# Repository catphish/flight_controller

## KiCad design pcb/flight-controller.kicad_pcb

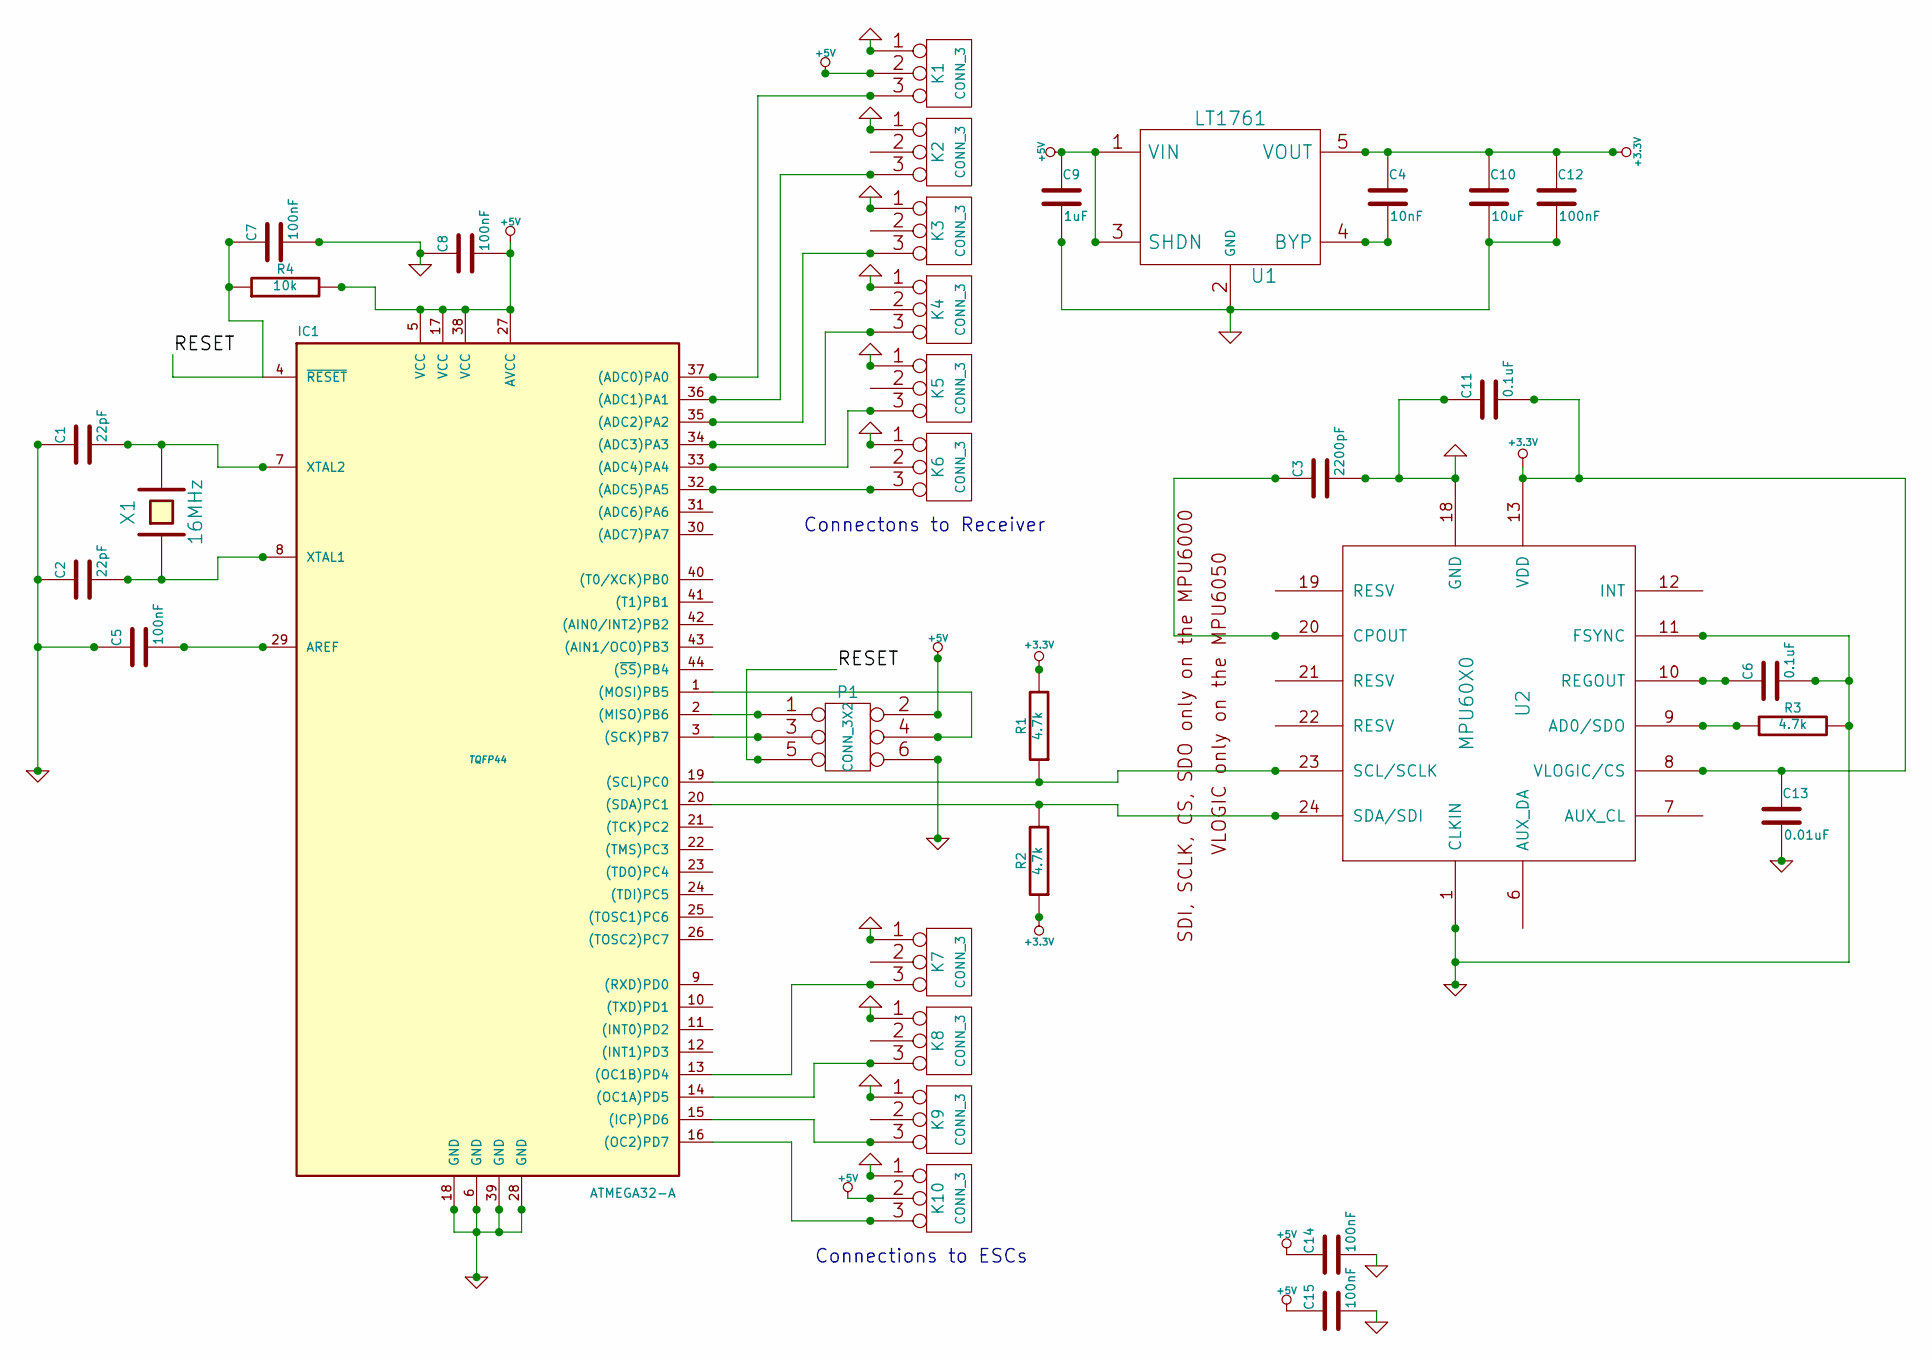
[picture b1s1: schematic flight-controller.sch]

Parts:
C1, C2: 22pF
C3: 2200pF
C4: 10nF
C5, C7, C8, C12, C14, C15: 100nF
C6, C11: 0.1uF
C9: 1uF
C10: 10uF
C13: 0.01uF
IC1: ATMEGA32-A; TQFP44
K1, K2, K3, K4, K5, K6, K7, K8, K9, K10: CONN_3
P1: CONN_3X2
R1, R2, R3: 4.7k
R4: 10k
U1: LT1761
U2: MPU60X0
X1: 16MHz

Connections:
+3.3V: C4.1, C10.1, C11.2, C12.1, C13.1, R1.2, R2.1, U1.5 (VOUT), U2.8 (VLOGIC/CS), U2.13 (VDD)
+5V: C8.2, C9.1, C14.1, C15.1, IC1.5 (VCC), IC1.17 (VCC), IC1.27 (AVCC), IC1.38 (VCC), K1.2 (PM), K10.2 (PM), P1.2, R4.2, U1.1 (VIN), U1.3 (SHDN)
/RESET: C7.1, IC1.4 (~RESET), P1.5, R4.1
GND: C1.1, C2.1, C3.2, C5.1, C6.2, C7.2, C8.1, C9.2, C10.2, C11.1, C12.2, C13.2, C14.2, C15.2, IC1.6 (GND), IC1.18 (GND), IC1.28 (GND), IC1.39 (GND), K1.1, K2.1, K3.1, K4.1, K5.1, K6.1, K7.1, K8.1, K9.1, K10.1, P1.6, R3.2, U1.2 (GND), U2.1 (CLKIN), U2.11 (FSYNC), U2.18 (GND)
unnamed: IC1.13 ((OC1B)PD4), K7.3
unnamed: IC1.14 ((OC1A)PD5), K8.3
unnamed: C5.2, IC1.29 (AREF)
unnamed: IC1.20 ((SDA)PC1), R2.2, U2.24 (SDA/SDI)
unnamed: IC1.19 ((SCL)PC0), R1.1, U2.23 (SCL/SCLK)
unnamed: IC1.37 ((ADC0)PA0), K1.3
unnamed: IC1.36 ((ADC1)PA1), K2.3
unnamed: IC1.35 ((ADC2)PA2), K3.3
unnamed: IC1.34 ((ADC3)PA3), K4.3
unnamed: IC1.33 ((ADC4)PA4), K5.3
unnamed: IC1.32 ((ADC5)PA5), K6.3
unnamed: IC1.16 ((OC2)PD7), K10.3
unnamed: C3.1, U2.20 (CPOUT)
unnamed: IC1.1 ((MOSI)PB5), P1.4
unnamed: C6.1, U2.10 (REGOUT)
unnamed: R3.1, U2.9 (AD0/SDO)
unnamed: C4.2, U1.4 (BYP)
unnamed: IC1.2 ((MISO)PB6), P1.1
unnamed: IC1.3 ((SCK)PB7), P1.3
unnamed: C1.2, IC1.7 (XTAL2), X1.2
unnamed: IC1.15 ((ICP)PD6), K9.3
unnamed: C2.2, IC1.8 (XTAL1), X1.1

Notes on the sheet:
Connections to ESCs
Connectons to Receiver

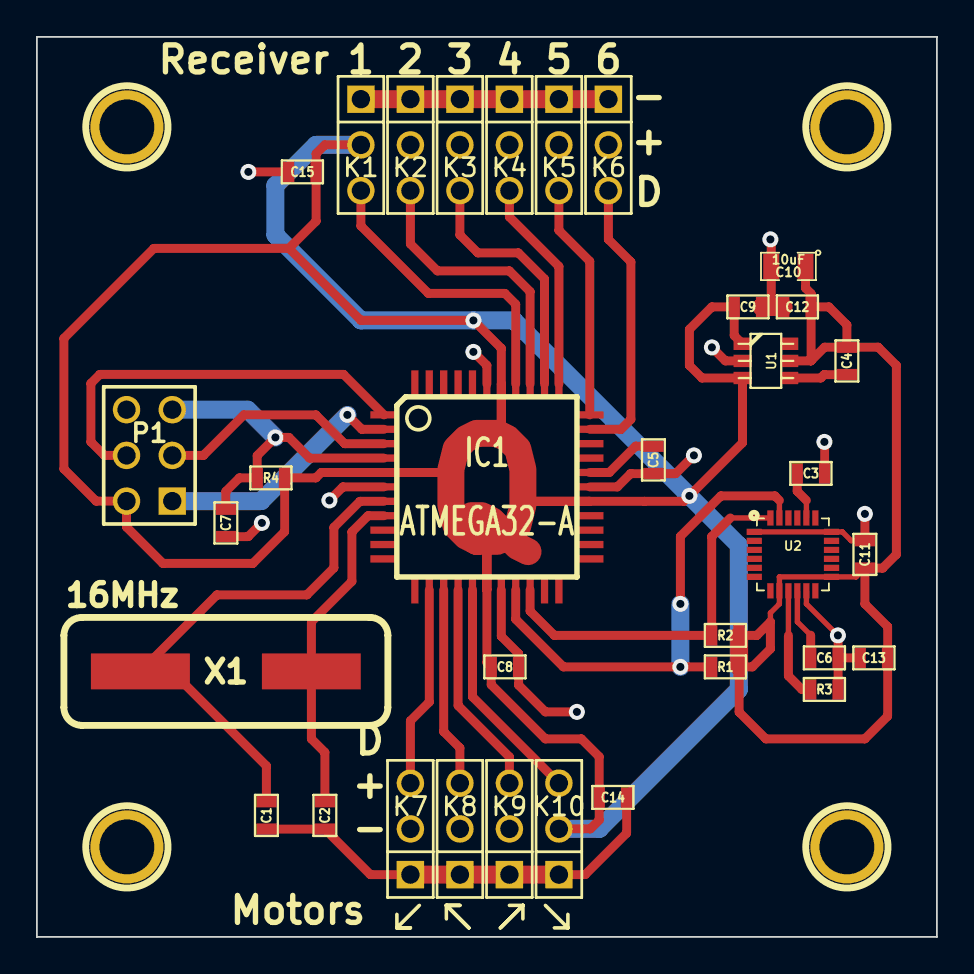
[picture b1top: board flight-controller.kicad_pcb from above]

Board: 2 copper layers, 50.0 x 50.0 mm, 34 parts (0 on the bottom side), 26 nets.

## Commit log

2013-11-17 Initial attempt with R/C and basic stabilization
2013-11-17 lots of work, partially functional / tested stabilization, currently FWD
2013-11-18 add a proper PID algorithm because my stabilization sucked, untested
2013-11-18 tune the thingy
2013-11-18 today i learned motor speeds reduce with battery voltage, we need to scale everything together
2013-11-23 rewrite motor and radio code for speed / accuracy
2013-11-23 fuck me, it's stable like this
2013-11-23 tidying, adjustments proportional to throttle
2013-11-23 minor tweaks
2013-11-24 live pid graphs, don't adjust pid when idling
2013-11-26 disable slow barometer, insert some simple PID values, add z stabilization
2013-11-26 battery voltage read
2013-11-26 high speed barometer code, remove ineffective z-compensation
2013-11-28 small tidy
2013-11-28 major refactor, remove 3rd party PID, extract libraries
2013-11-28 remove hardcoded test value
2013-11-28 i'm committing because i just had an actual successful flight!
2013-11-28 add z stabilization and control
2013-11-28 don't invert Y axis, that causes pain when you try to fly it away from your face
2013-11-28 these were way too sensitive
2013-11-29 correct fatal error with reversed gyro, increase control sensitivity
2013-12-01 tidy up, add scope for I term on z drift
2013-12-03 tidy things up, remove unused code, add 6-channel receiver, add kill switch to allow further reductions in throttle sensitivity
2013-12-03 further tidying
2013-12-03 remove failed altitude experimental code
2013-12-06 adjust controller responses
2013-12-07 altitude hold
2013-12-07 remove altitude hold, this isn't working well
2013-12-07 increase control sensitivity
2013-12-07 large increases to control and feedback responsiveness
2013-12-07 further pid tuning
2013-12-07 more pid tuning, we can now achieve stable flight, with all controls being very rsonsive and the throttle still a little oversensitive
2013-12-08 add compass, not currently accurate
2013-12-08 re-add altitude hold, this isn't tested, but will only be active if enabled from the RC
2013-12-10 lots of work on altitude control, UNTESTED
2013-12-12 Revert "lots of work on altitude control, UNTESTED"
    This reverts commit 00f80fb907816c0848a73623b2992b4bc48d4b41.
2013-12-12 Revert "re-add altitude hold, this isn't tested, but will only be active if enabled from the RC"
    This reverts commit 7fdb75e066b343deceeb1af1b908b9b1dafb5d2a.
2013-12-13 begin support for echo distance sensor
2013-12-14 more sensitive barometer response
2013-12-14 simultaneous ESC updates for faster and more consistent response, add pitch/roll to throttle to prevent descent when manoeuvring, increse altitude hold sensitivity
2013-12-16 replace BMP085 with MS5611, rework altitude hold
2013-12-22 significant tidying in preparation of basic hardware build
2013-12-22 add schematic / pcb layout
2013-12-22 lots of improvements to flight control and PCB
2013-12-22 add rendered pcb PDFs
2013-12-27 minor improvements, this should improve descent stability
2013-12-29 proper rate based yaw, altitude correction linked to ch6
2013-12-29 documentation and tidying
2013-12-30 finish yaw control, tune altitude correction
2013-12-31 detect upside-down state, reduce yaw correction at extremes of angle
2014-01-06 complete rewrite without arduino
2014-01-09 finish avr version
2014-01-10 adjust gains, use DMP to fetch filtered gyro outputs
2014-03-02 various improvements, currently running on arduino mega
2014-03-02 update copyright notices
2014-03-17 add very simple altitude control using MS5611
2014-03-17 remove pcb for now
2014-03-19 velocity and altitude estimates using apu and baro
2014-03-19 finish baro altitude hold, accurate to approx 1m, may need gain adjustments
2014-03-19 gyro calibration
2014-03-20 final tuning for baro alt. TODO: alt gains (alt vs velocity)
2014-03-22 small tuning adjustments
2014-03-23 increase yaw correction
2014-03-23 tuning
2014-03-26 a slightly different tae on altitude tuning
2014-03-30 new digital rc, small tunings
2014-03-30 small tuning changes, very stable flight, yaw control is a little dangerous
2014-04-01 a totally new take on altitude hold, safer yaw correction, i currently have concerns about pitch/roll integration
2014-04-02 undo some non working things
2014-04-02 Revert "undo some non working things"
    This reverts commit e10c75d29966ebf9c649589e917734910f83a39f.
2014-04-02 Revert "a totally new take on altitude hold, safer yaw correction, i currently have concerns about pitch/roll integration"
    This reverts commit 72d18917e2496c67f50c0db7bd1784adafcd640c.
2014-04-02 sort out some bits
2014-04-05 add compass (probably finished) and gps (not finished)
2014-04-06 pretty sure that was invested!
2014-04-06 calibrate gyro / z-accelerometer
2014-04-06 a little more accelerometer tweaking
2014-04-06 new high resolution compass assisted yaw control, untested, improvements to altitude hold algorithm, untested
2014-04-08 revert previous altitude hold changes, old version was better NOTE: compass way off when pitching forward/back NOTE: GPS seems to work, but inaccurate due to compass pitch issue NOTE: GPS adjustments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
2014-04-10 tidy, this isn't going to work without a 10DOF board
2014-04-12 better compass calculations, tuning, gps fix NOTE: GPS should now work, but results are awful, probably needs a PID
2014-04-12 minor improvements, abandon gps for now
2014-04-12 fix gps x/y and re-enable
